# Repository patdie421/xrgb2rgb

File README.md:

# Goal of this converter
This card convert TTL RGB (xRGB / TTLLS / ... from some Apple IIe cards or Apple ///) to "standard" RGB. Color are not exactly the same as the Apple IIe color palette but it's usable !  
It was designed for my Taxan Model 410-80 card to chaine it with a PCT Colorswitch (see https://github.com/patdie421/pct-connectors-rebuild/blob/main/README.md).  
It should work for other kind of card who can be connected to Taxan RGBvision (mode II), AppleColour (AppleColor) 100 monitor or equivalent.  
The converter is base on the output stage circuit of the Chat Mauve EVE Card (https://mirrors.apple2.org.za/ftp.apple.asimov.net/documentation/hardware/video/Le%20Chat%20Mauve%20-%20Manuel%20de%20re_25cc_2581fe_25cc_2581rence.pdf).  
# Working status
- Apple II GS Color monitor direct connexion: tested, working
- Apple II GS Color monitor via PCT Colorswitch: tested, working
- Scart TV/Monitor: not tester (use at your own risk ... like all usual :-) )
- Other RGB monitor: can't be tested (but will be done), I have only an Apple II GS monitor ... (give me feedback, please)  
# usefull link
- https://hobbytronics.home.blog/2024/12/21/apple-iigs-rgb-monitor-scart-cable/
- https://apple3.org/Documents/Schematics/ConsortiRGB.png
- https://mirrors.apple2.org.za/ftp.apple.asimov.net/documentation/hardware/video/AppleService%20Technical%20Procedures%20-%20AppleColor%20Monitor%20100.pdf

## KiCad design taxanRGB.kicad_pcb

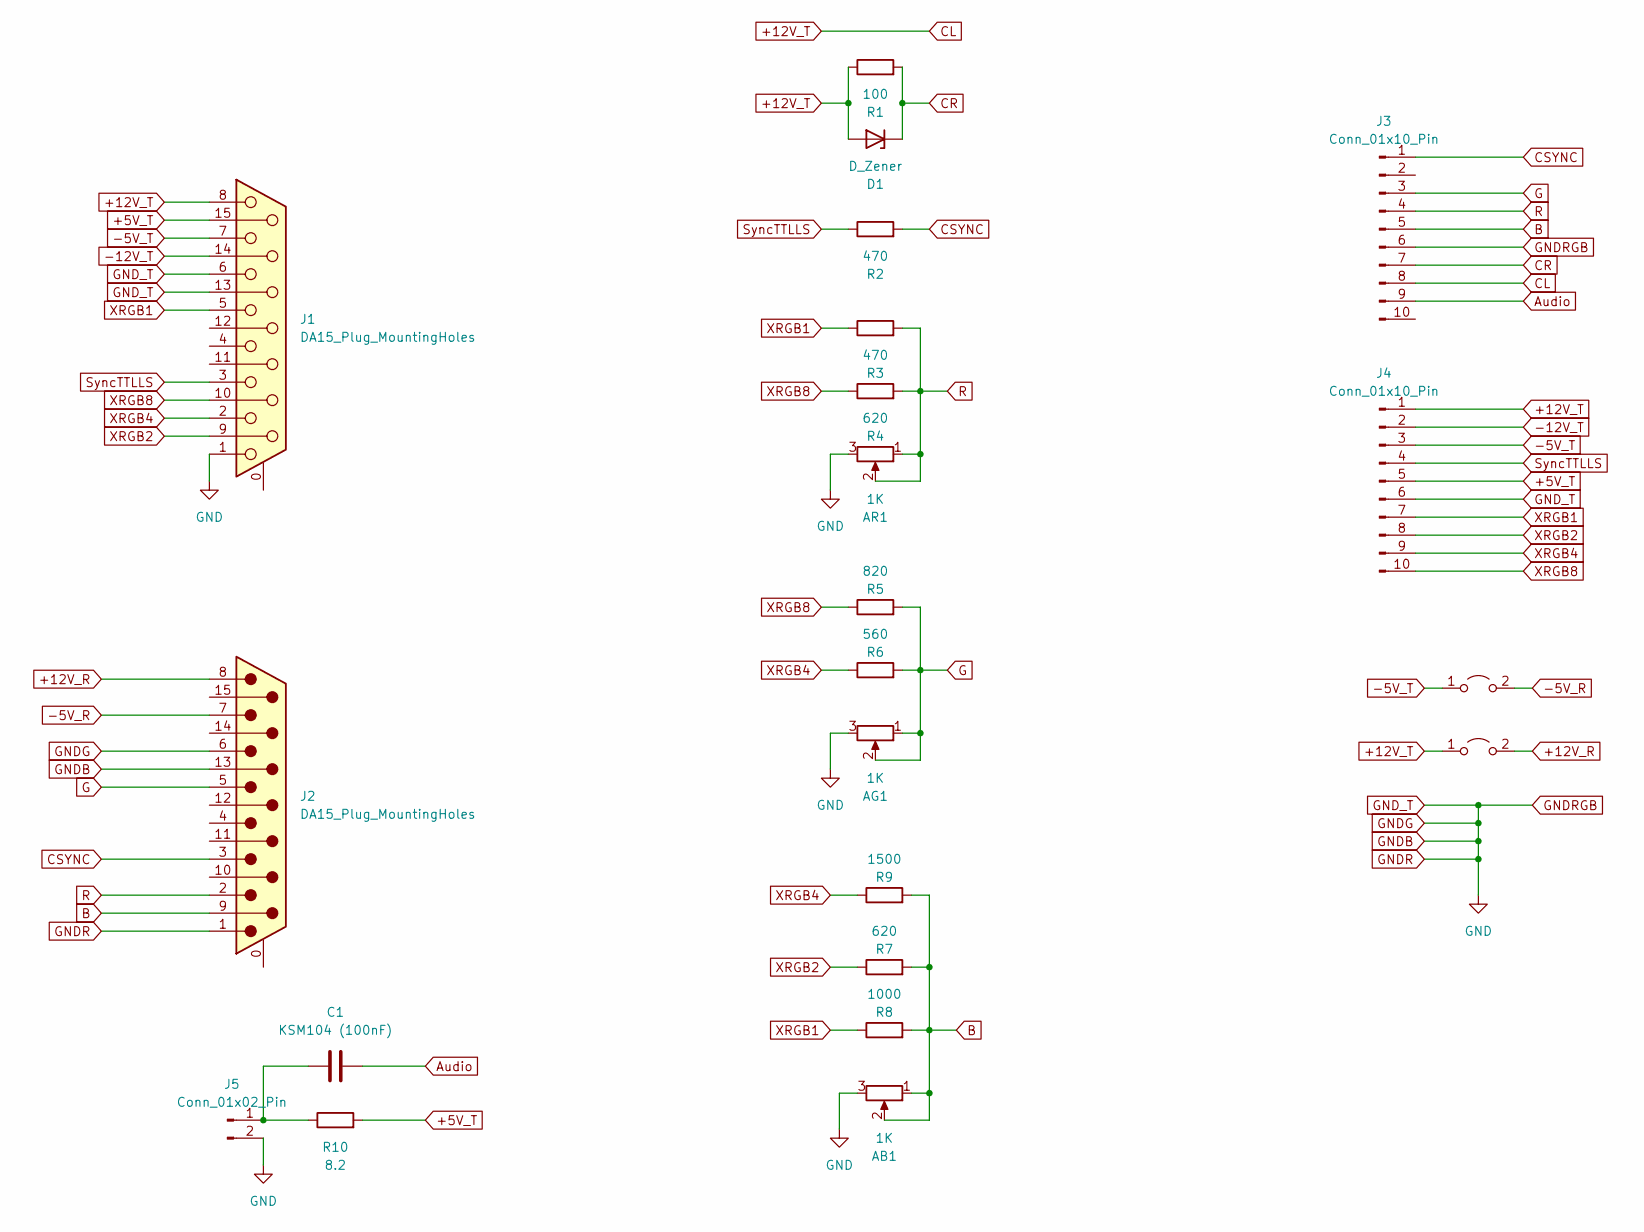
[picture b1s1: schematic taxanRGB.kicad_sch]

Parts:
AB1: 1K; Potentiometer_Piher_PT-10-V10_Vertical
AG1: 1K; Potentiometer_Piher_PT-10-V10_Vertical
AR1: 1K; Potentiometer_Piher_PT-10-V10_Vertical
C1: KSM104 (100nF); C_Disc_D4.3mm_W1.9mm_P5.00mm
D1: D_Zener; D_DO-34_SOD68_P10.16mm_Horizontal
J1: DA15_Plug_MountingHoles; DSUB-15_Male_EdgeMount_P2.77mm
J2: DA15_Plug_MountingHoles; DSUB-15_Female_EdgeMount_P2.77mm
J3, J4: Conn_01x10_Pin; PinHeader_1x10_P2.54mm_Vertical
J5: Conn_01x02_Pin; PinHeader_1x02_P2.54mm_Vertical
JP1, JP2: Jumper_2_Open; SolderJumper-2_P1.3mm_Open_TrianglePad1.0x1.5mm
R1: 100; R_Axial_DIN0309_L9.0mm_D3.2mm_P12.70mm_Horizontal
R2, R3: 470; R_Axial_DIN0309_L9.0mm_D3.2mm_P12.70mm_Horizontal
R4, R7: 620; R_Axial_DIN0309_L9.0mm_D3.2mm_P12.70mm_Horizontal
R5: 820; R_Axial_DIN0309_L9.0mm_D3.2mm_P12.70mm_Horizontal
R6: 560; R_Axial_DIN0309_L9.0mm_D3.2mm_P12.70mm_Horizontal
R8: 1000; R_Axial_DIN0309_L9.0mm_D3.2mm_P12.70mm_Horizontal
R9: 1500; R_Axial_DIN0309_L9.0mm_D3.2mm_P12.70mm_Horizontal
R10: 8.2; R_Axial_DIN0309_L9.0mm_D3.2mm_P12.70mm_Horizontal

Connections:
+5V_T: J1.15, J4.5, R10.2
+12V_R: J2.8, JP2.2 (B)
+12V_T: D1.2 (A), J1.8, J3.8, J4.1, JP2.1 (A), R1.1
-5V_R: J2.7, JP1.2 (B)
-5V_T: J1.7, J4.3, JP1.1 (A)
-12V_T: J1.14, J4.2
Audio: C1.1, J3.9
B: AB1.1, AB1.2, J2.9, J3.5, R7.2, R8.2, R9.2
CR: D1.1 (K), J3.7, R1.2
CSYNC: J2.3, J3.1, R2.2
G: AG1.1, AG1.2, J2.5, J3.3, R5.2, R6.2
GNDB: AB1.3, AG1.3, AR1.3, J1.1, J1.6, J1.13, J2.1, J2.6, J2.13, J3.6, J4.6, J5.2
unnamed: C1.2, J5.1, R10.1
R: AR1.1, AR1.2, J2.2, J3.4, R3.2, R4.2
SyncTTLLS: J1.3, J4.4, R2.1
XRGB1: J1.5, J4.7, R3.1, R8.1
XRGB2: J1.9, J4.8, R7.1
XRGB4: J1.2, J4.9, R6.1, R9.1
XRGB8: J1.10, J4.10, R4.1, R5.1

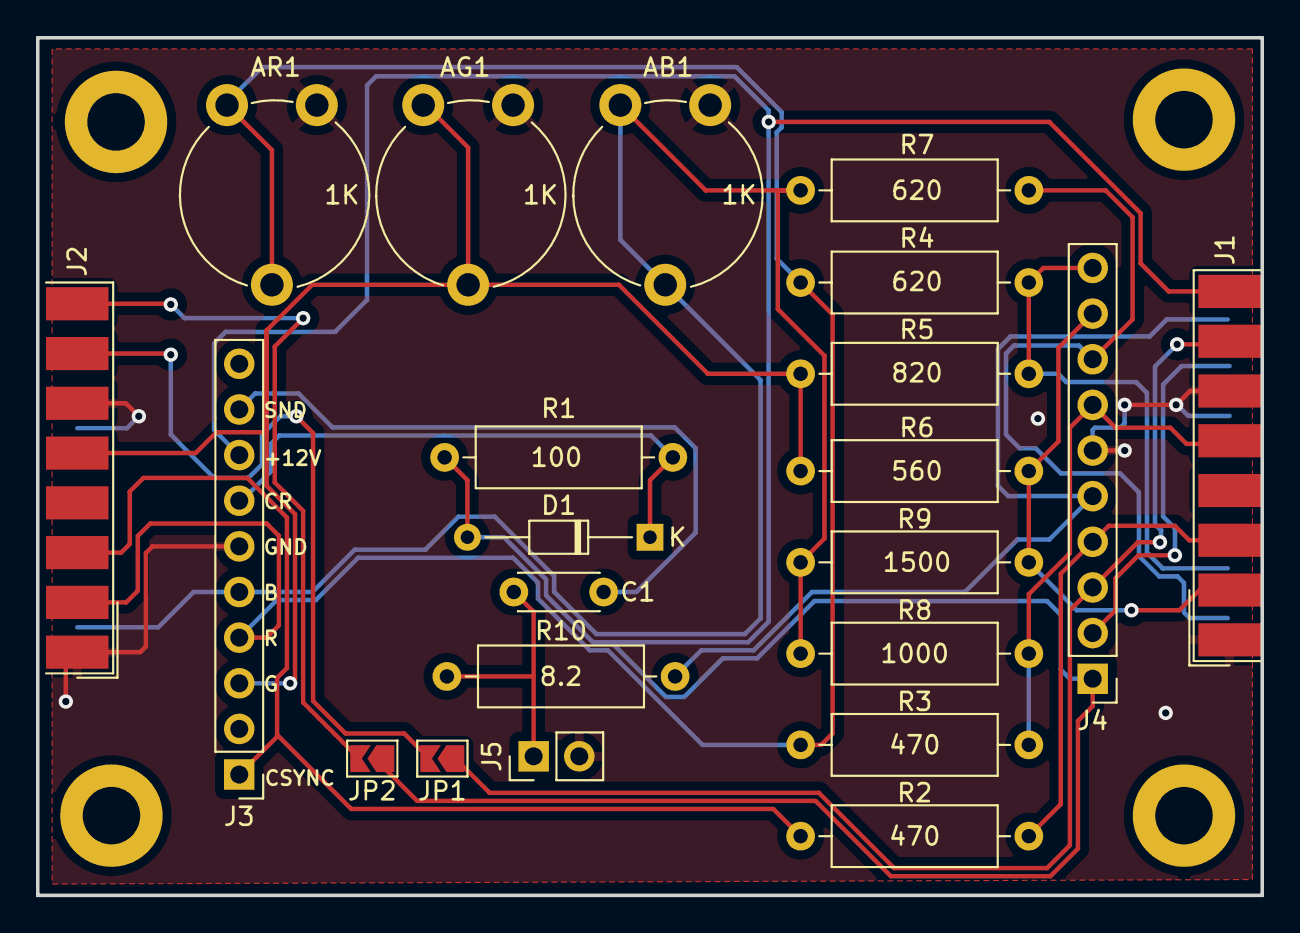
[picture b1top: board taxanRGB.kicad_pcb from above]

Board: 2 copper layers, 68.2 x 47.7 mm, 22 parts (0 on the bottom side), 19 nets.
